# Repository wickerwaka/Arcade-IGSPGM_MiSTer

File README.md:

# This repository now lives in the [MiSTer organization](https://github.com/mister-devel/Arcade-IGSPGM_MiSTer)

# IGS PolyGame Master MiSTer FPGA core

The PolyGame Master (PGM) is an arcade system board released in 1997 by IGS. It has a lot of similarities to SNK's Neo Geo - cartridge based with multiple buses, heavily sprite focused graphics hardware, 68000 main CPU, Z80 for audio.

- Main processor: Motorola 68000 @ 20 MHz
- Sound processor: Zilog Z80 @ 8.4 MHz
- Sound chip: Wavefront ICS2115
- Graphics chip: IGS023

Games come with several flavors of protection hardware on the cartridge. Most feature an ARM7 CPU and in later games the ARM takes on a larger portion of the game update processing.

## Status
This core is currently BETA. Most games work, but the core needs more testing. The PGM platform features a large amount of variants and bootlegs that all require testing. If you encounter issues please report them via github. Save state files can be especially useful for tracking down and reproducing issues, so if you have some then please include them.

## Core Features
- Save States. The core supports save states for all games. It is expected that you can save and restore a save state at any point. If you encounter issues restoring save states, please report them.
- H-Scale. The PGM video signal tends to be squashed horizontally by consumer CRTs. In the Video Settings menu there is an H-Scale option that can be enabled which allows you to scale the width of the image up and down. This only works for analog video and does not play well with the HDMI scaler.
- NVRAM. The 128KB of main RAM on the PGM is battery backed. On the original system this is often used for bookkeeping data such as earning per game. Some games (CAVE shooters) use it for storing per-game settings. It might also be used for high score saving by some games.
- RTC. The PGM also has a battery backed clock. As far as I know this is not used by any games, but it does get displayed at startup by the BIOS. The timer can be adjusted in the BIOS, but at startup it will always be set to the MiSTers current system time.

## Supported games

- Oriental Legend
- Oriental Legend Super
- Dragon World 3
- Dragon World 3 EX
- Dragon World 2001
- The Killing Blade
- The Killing Blade Plus
- Photo Y2K
- Knights of Valour Super Heroes
- Knights of Valour 2
- Martial Masters
- Demon Front
- The Gladiator
- S.V.G. - Spectral vs Generation
- DoDonPachi II - Bee Storm
- DoDonPachi III / Dai-Ou-Jou
- Ketsui: Kizuna Jigoku Tachi
- Espgaluda

## Not yet working

- Knights of Valour
- Knights of Valour Plus
- Knights of Valour 2 Plus - Nine Dragons
- Dragon World Pretty Chance
- Happy 6-in-1

## Sources
Multiple different sources have been used as reference when developing this core.

[MAME](https://www.mamedev.org/) - Tons of information about the PGM system and especially its protection mechanisms. Also used as the source for the initial ICS2115 implementation.

[igspgm.com](https://igspgm.com/) - Motherboard images, cartridge images, archived documents. Super valuable archive of information that could easily have been lost to history.

[PGMTech](https://github.com/laoo/PGMTech) - Solid documentation of PGM memory maps and system architecture

[GUS GF1 Decap](https://github.com/nukeykt/LPC-GUS) - Coming from the same hardware lineage, the GF1 source was a useful reference for how things might be done inside the ICS2115

[Game Bub](https://github.com/elipsitz/gamebub) - ARM7TDMI implementation

## Special Thanks
Thanks to [James](https://www.retrohq.co.uk/) for all the additional insights he was able to provide. The stars aligned and we ended up exploring parts of the system as the same time. I hope I was able to help him half as much as he helped me.

Thanks to [Tim](https://igspgm.com/) for keeping valuable sources of PGM information alive on the internet over the years. It has been an invaluable source of information.

laoo, Xolod, augitesoul and everyone who has playtested, provided feedback and/or support.

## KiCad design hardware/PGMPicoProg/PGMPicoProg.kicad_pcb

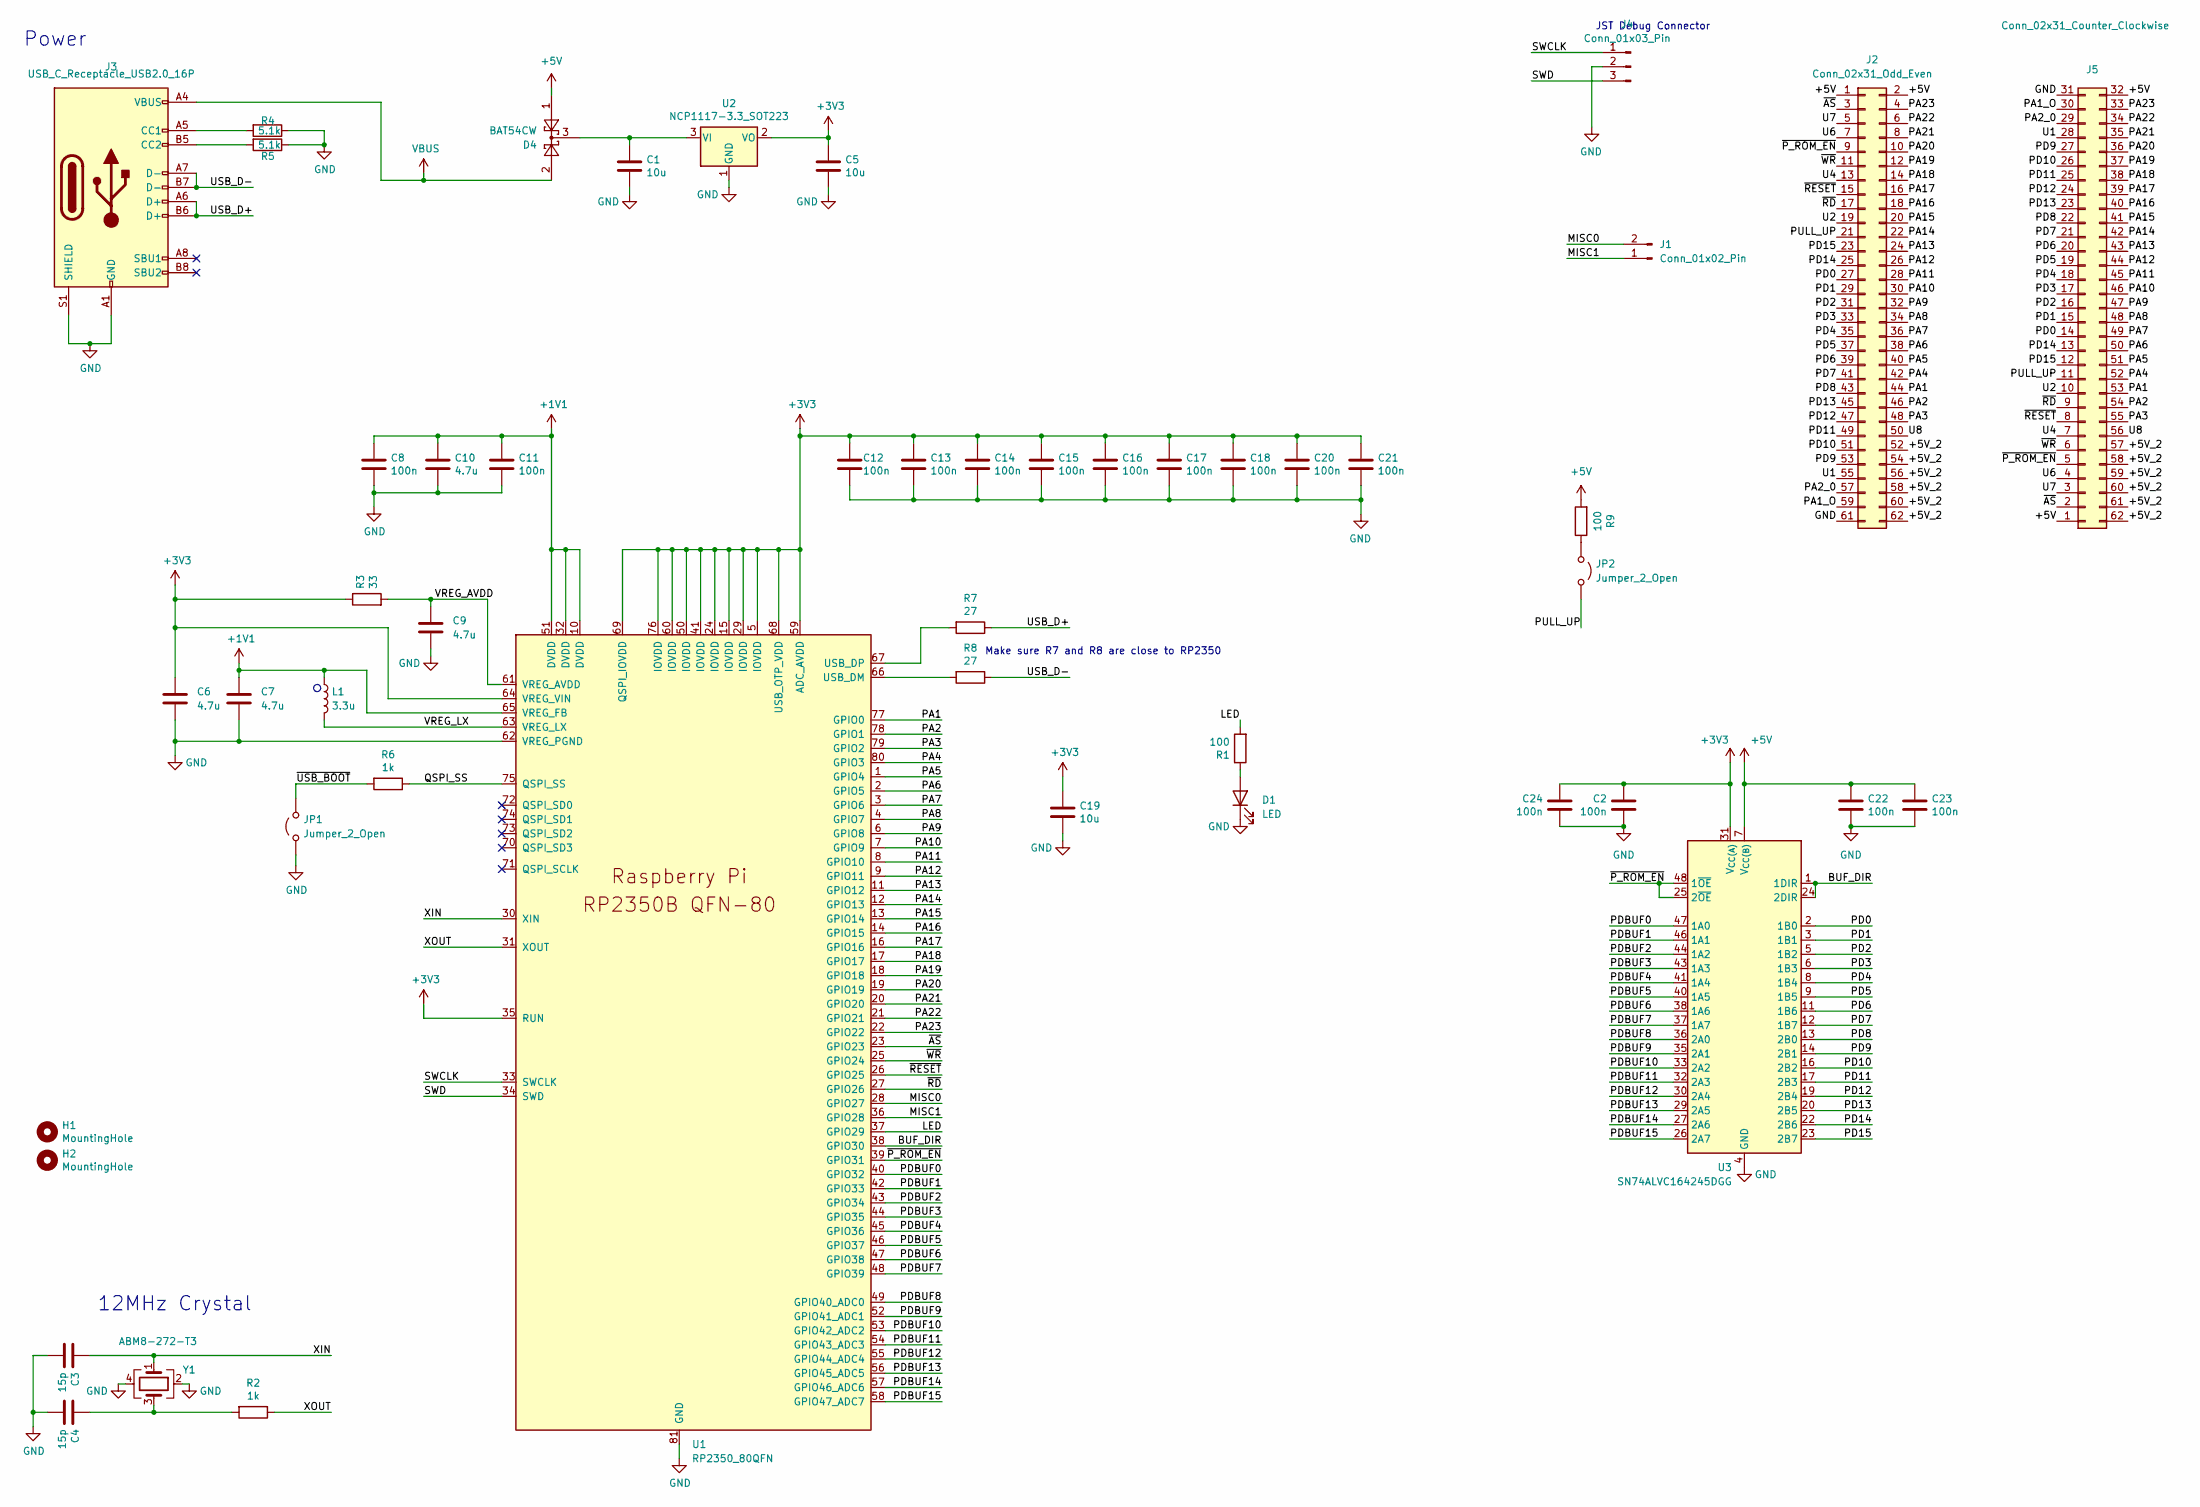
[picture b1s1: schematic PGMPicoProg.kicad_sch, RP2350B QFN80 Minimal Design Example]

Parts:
C1, C5, C19: 10u; C_0805_2012Metric; LCSC Part C15850
C2, C8, C11, C12, C13, C14, C15, C16, C17, C18, C20, C21, C22, C23, C24: 100n; C_0402_1005Metric; LCSC Part C1525
C3, C4: 15p; C_0402_1005Metric; LCSC Part C1548
C6, C7: 4.7u; C_0402_1005Metric_small_pads; LCSC Part C23733
C9, C10: 4.7u; C_0402_1005Metric; LCSC Part C23733
D1: LED; LED_0805_2012Metric; LCSC Part C2297
D4: BAT54CW; SOT-323_SC-70; MPN# C22392482; LCSC Part C22392482
H1, H2: MountingHole; MountingHole_2.7mm_M2.5
J1: Conn_01x02_Pin; PinHeader_1x02_P2.54mm_Vertical
J2: Conn_02x31_Odd_Even; PinHeader_2x31_P2.54mm_Vertical
J3: USB_C_Receptacle_USB2.0_16P; USB_C_Receptacle_G-Switch_GT-USB-7010ASV; LCSC Part C2988369
J4: Conn_01x03_Pin; PinHeader_1x03_P2.54mm_Vertical
J5: Conn_02x31_Counter_Clockwise; PGM_Cart
JP1, JP2: Jumper_2_Open; PinHeader_1x02_P2.54mm_Vertical
L1: 3.3u; L_pol_2016; LCSC Part C42411119
R1, R9: 100; R_0402_1005Metric; LCSC Part C25076
R2, R6: 1k; R_0402_1005Metric; LCSC Part C11702
R3: 33; R_0402_1005Metric; LCSC Part C25105
R4, R5: 5.1k; R_0402_1005Metric; LCSC Part C25905
R7, R8: 27; R_0402_1005Metric; LCSC Part C25100
U1: RP2350_80QFN; RP2350-QFN-80-1EP_10x10_P0.4mm_EP3.4x3.4mm_ThermalVias; LCSC Part C39843328
U2: NCP1117-3.3_SOT223; SOT-223-3_TabPin2; LCSC Part C6186
U3: SN74ALVC164245DGG; TSSOP-48_6.1x12.5mm_P0.5mm; LCSC Part C4364184
Y1: ABM8-272-T3; Crystal_SMD_3225-4Pin_3.2x2.5mm; LCSC Part C20625731

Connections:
+1V1: C7.1, C8.1, C10.1, C11.1, L1.1, U1.10 (DVDD), U1.32 (DVDD), U1.51 (DVDD), U1.65 (VREG_FB)
+3V3: C2.1, C5.1, C6.1, C12.1, C13.1, C14.1, C15.1, C16.1, C17.1, C18.1, C19.1, C20.1, C21.1, C24.1, R3.1, U1.5 (IOVDD), U1.15 (IOVDD), U1.24 (IOVDD), U1.29 (IOVDD), U1.35 (RUN), U1.41 (IOVDD), U1.50 (IOVDD), U1.59 (ADC_AVDD), U1.60 (IOVDD), U1.64 (VREG_VIN), U1.68 (USB_OTP_VDD), U1.69 (QSPI_IOVDD), U1.76 (IOVDD), U2.2 (VO), U3.31 (V_{CC(A)}), U3.42 (V_{CC(A)})
+5V: C22.1, C23.1, D4.1, J2.1, J2.2, J5.1, J5.32, R9.2, U3.7 (V_{CC(B)}), U3.18 (V_{CC(B)})
/+5V_2: J2.52, J2.54, J2.56, J2.58, J2.60, J2.62, J5.57, J5.58, J5.59, J5.60, J5.61, J5.62
/BUF_DIR: U1.38 (GPIO30), U3.1 (1DIR), U3.24 (2DIR)
/LED: R1.2, U1.37 (GPIO29)
/MISC0: J1.2, U1.28 (GPIO27)
/MISC1: J1.1, U1.36 (GPIO28)
/PA1: J2.44, J5.53, U1.77 (GPIO0)
/PA1_O: J2.59, J5.30
/PA2: J2.46, J5.54, U1.78 (GPIO1)
/PA2_0: J2.57, J5.29
/PA3: J2.48, J5.55, U1.79 (GPIO2)
/PA4: J2.42, J5.52, U1.80 (GPIO3)
/PA5: J2.40, J5.51, U1.1 (GPIO4)
/PA6: J2.38, J5.50, U1.2 (GPIO5)
/PA7: J2.36, J5.49, U1.3 (GPIO6)
/PA8: J2.34, J5.48, U1.4 (GPIO7)
/PA9: J2.32, J5.47, U1.6 (GPIO8)
/PA10: J2.30, J5.46, U1.7 (GPIO9)
/PA11: J2.28, J5.45, U1.8 (GPIO10)
/PA12: J2.26, J5.44, U1.9 (GPIO11)
/PA13: J2.24, J5.43, U1.11 (GPIO12)
/PA14: J2.22, J5.42, U1.12 (GPIO13)
/PA15: J2.20, J5.41, U1.13 (GPIO14)
/PA16: J2.18, J5.40, U1.14 (GPIO15)
/PA17: J2.16, J5.39, U1.16 (GPIO16)
/PA18: J2.14, J5.38, U1.17 (GPIO17)
/PA19: J2.12, J5.37, U1.18 (GPIO18)
/PA20: J2.10, J5.36, U1.19 (GPIO19)
/PA21: J2.8, J5.35, U1.20 (GPIO20)
/PA22: J2.6, J5.34, U1.21 (GPIO21)
/PA23: J2.4, J5.33, U1.22 (GPIO22)
/PD0: J2.27, J5.14, U3.2 (1B0)
/PD1: J2.29, J5.15, U3.3 (1B1)
/PD2: J2.31, J5.16, U3.5 (1B2)
/PD3: J2.33, J5.17, U3.6 (1B3)
/PD4: J2.35, J5.18, U3.8 (1B4)
/PD5: J2.37, J5.19, U3.9 (1B5)
/PD6: J2.39, J5.20, U3.11 (1B6)
/PD7: J2.41, J5.21, U3.12 (1B7)
/PD8: J2.43, J5.22, U3.13 (2B0)
/PD9: J2.53, J5.27, U3.14 (2B1)
/PD10: J2.51, J5.26, U3.16 (2B2)
/PD11: J2.49, J5.25, U3.17 (2B3)
/PD12: J2.47, J5.24, U3.19 (2B4)
/PD13: J2.45, J5.23, U3.20 (2B5)
/PD14: J2.25, J5.13, U3.22 (2B6)
/PD15: J2.23, J5.12, U3.23 (2B7)
/PDBUF0: U1.40 (GPIO32), U3.47 (1A0)
/PDBUF1: U1.42 (GPIO33), U3.46 (1A1)
/PDBUF2: U1.43 (GPIO34), U3.44 (1A2)
/PDBUF3: U1.44 (GPIO35), U3.43 (1A3)
/PDBUF4: U1.45 (GPIO36), U3.41 (1A4)
/PDBUF5: U1.46 (GPIO37), U3.40 (1A5)
/PDBUF6: U1.47 (GPIO38), U3.38 (1A6)
/PDBUF7: U1.48 (GPIO39), U3.37 (1A7)
/PDBUF8: U1.49 (GPIO40_ADC0), U3.36 (2A0)
/PDBUF9: U1.52 (GPIO41_ADC1), U3.35 (2A1)
/PDBUF10: U1.53 (GPIO42_ADC2), U3.33 (2A2)
/PDBUF11: U1.54 (GPIO43_ADC3), U3.32 (2A3)
/PDBUF12: U1.55 (GPIO44_ADC4), U3.30 (2A4)
/PDBUF13: U1.56 (GPIO45_ADC5), U3.29 (2A5)
/PDBUF14: U1.57 (GPIO46_ADC6), U3.27 (2A6)
/PDBUF15: U1.58 (GPIO47_ADC7), U3.26 (2A7)
/PULL_UP: J2.21, J5.11, JP2.2 (B)
/QSPI_SS: R6.1, U1.75 (QSPI_SS)
/SWCLK: J4.1, U1.33 (SWCLK)
/SWD: J4.3, U1.34 (SWD)
/U1: J2.55, J5.28
/U2: J2.19, J5.10
/U4: J2.13, J5.7
/U6: J2.7, J5.4
/U7: J2.5, J5.3
/U8: J2.50, J5.56
/USB_D+: J3.A6 (D+), J3.B6 (D+), R7.1
/USB_D-: J3.A7 (D-), J3.B7 (D-), R8.1
/VREG_AVDD: C9.1, R3.2, U1.61 (VREG_AVDD)
/VREG_LX: L1.2, U1.63 (VREG_LX)
/XIN: C3.1, U1.30 (XIN), Y1.1
/XOUT: R2.1, U1.31 (XOUT)
/~AS: J2.3, J5.2, U1.23 (GPIO23)
/~P_ROM_EN: J2.9, J5.5, U1.39 (GPIO31), U3.25 (2~OE), U3.48 (1~OE)
/~RD: J2.17, J5.9, U1.27 (GPIO26)
/~RESET: J2.15, J5.8, U1.26 (GPIO25)
/~USB_BOOT: JP1.2 (B), R6.2
/~WR: J2.11, J5.6, U1.25 (GPIO24)
GND: C1.2, C2.2, C3.2, C4.2, C5.2, C6.2, C7.2, C8.2, C9.2, C10.2, C11.2, C12.2, C13.2, C14.2, C15.2, C16.2, C17.2, C18.2, C19.2, C20.2, C21.2, C22.2, C23.2, C24.2, D1.1 (K), J2.61, J3.A1 (GND), J3.A12 (GND), J3.B1 (GND), J3.B12 (GND), J3.S1 (SHIELD), J4.2, J5.31, JP1.1 (A), R4.1, R5.1, U1.62 (VREG_PGND), U1.81 (GND), U2.1 (GND), U3.4 (GND), U3.10 (GND), U3.15 (GND), U3.21 (GND), U3.28 (GND), U3.34 (GND), U3.39 (GND), U3.45 (GND), Y1.2, Y1.4
unnamed: C4.1, R2.2, Y1.3
unnamed: D1.2 (A), R1.1
unnamed: J3.A5 (CC1), R4.2
unnamed: J3.B5 (CC2), R5.2
unnamed: JP2.1 (A), R9.1
unnamed: R8.2, U1.66 (USB_DM)
unnamed: R7.2, U1.67 (USB_DP)
unnamed: C1.1, D4.3, U2.3 (VI)
VBUS: D4.2, J3.A4 (VBUS), J3.A9 (VBUS), J3.B4 (VBUS), J3.B9 (VBUS)

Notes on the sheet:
12MHz Crystal
JST Debug Connector
Make sure R7 and R8 are close to RP2350
Power

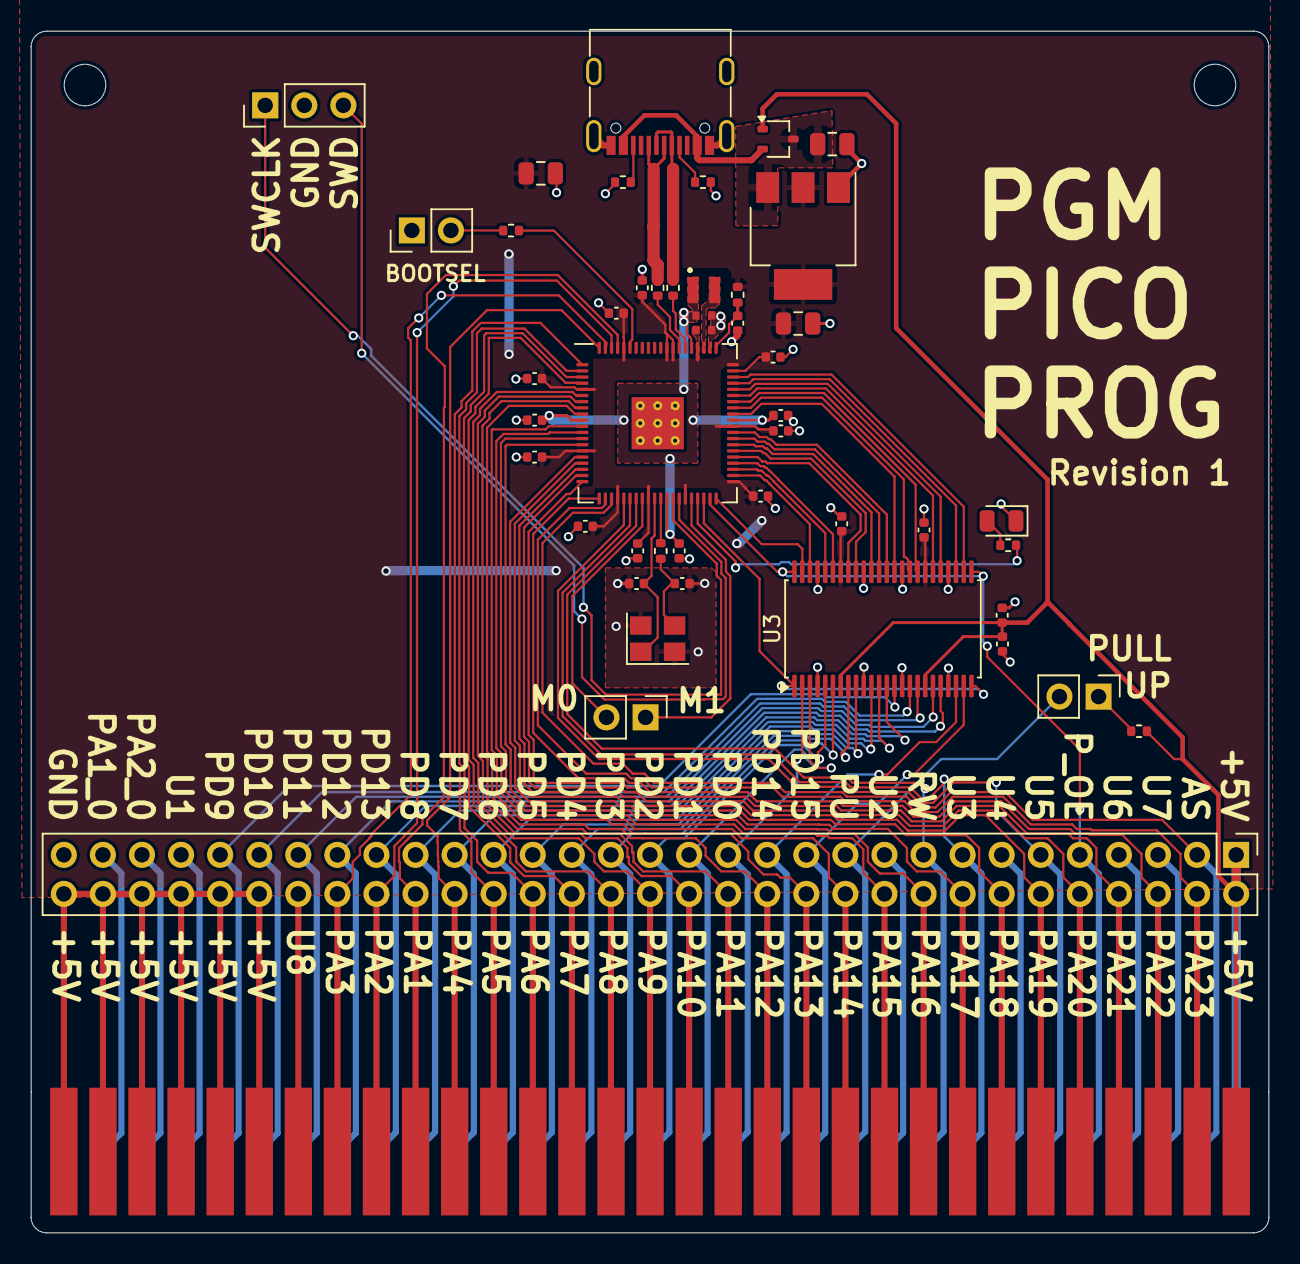
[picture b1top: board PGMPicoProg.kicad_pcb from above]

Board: 2 copper layers, 80.4 x 78.1 mm, 49 parts (0 on the bottom side), 97 nets.

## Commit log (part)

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2026-03-16 Initial commit Based on F2 core
2026-03-16 Switch IGS023 to 50Mhz clock and generate 10Mhz pixel clock internally
2026-03-21 Add some palette reading
2026-03-22 Correct h/v alignment
2026-03-22 Fixed DE-10 compilation
    Switch system clock to 50Mhz, SDRAM to 100Mhz
2026-03-22 Clean up M68000 state access in the simulator
2026-03-25 Hardware files for PGM Pico Prog and Passthrough Gartridge Module
2026-03-25 32x32 tile background layer first pass
2026-03-27 Add v3021 RTC timer and the beginnings of the Z80 related IGS026
2026-03-27 Add to files.qip
2026-03-27 Access audio RAM video igs026
2026-03-27 Rename igs026_z80 to igs026_x
2026-03-28 Sprite viewer
2026-03-29 ICS2115
2026-03-30 DE-10 fixes
2026-03-30 Fix addressing
2026-03-31 Update ICS2115 with read delay handling
2026-03-31 Flip audio endian. Fix SDR width
2026-04-11 Added additional test rom pages Fix save state support
2026-04-11 Added pgm_test rom to simulator Adjusted IRQ4 and 6 behavior to better match hardware
2026-04-12 Added test for irq4 performance. Confirmed timer continues to increment when irq is disabled. Updated core to match
2026-04-12 Scanline and IQR4 triggered on hsync
2026-04-12 refactor(sim): align naming with clang-tidy
2026-04-12 fix(pgmaudioextractor): use sdk usb reset interface
2026-04-13 Tick improvements
2026-04-13 refactor(sim): add controller API
2026-04-13 feat(sim): add stdio control protocol
2026-04-13 feat(sim): add server runtime mode
2026-04-13 feat(sim): extend agent control surface
2026-04-13 feat(sim): add VPI signal control
2026-04-13 feat(sim): add signal watches and input control
2026-04-13 refactor(sim): remove protocol exceptions
2026-04-14 fix(sim): shutdown server on eof
2026-04-14 fix(usb-audio): prevent ep panic on stream reopen
    Clear EP1 IN buffer control register in close callback to prevent
    USB_BUF_CTRL_AVAIL persisting across ISO endpoint reactivation on
    RP2040/RP2350. Also fix serial descriptor, add audio lifecycle
    instrumentation, and add reconnect-aware serial monitor tool.
2026-04-14 fix(rate): default USB sample rate to source clock
    Default the nominal capture rate to 33074 Hz and snap runtime
    measurement to the known 33074/44100 Hz source rates.
    Also update TODO.md to reflect the current MVP state and the
    remaining validation and cleanup work.
2026-04-15 refactor(capture): document and harden cdc extractor
    Document the native-rate CDC packet protocol, improve the host
    receiver with summary and gap reporting, remove the obsolete UAC
    implementation, and unify packet sequencing across audio and status
    packets.
    A 30-second strict capture check completed with zero packet and frame
    gaps on macOS.
2026-04-16 Add simulator audio capture commands and shared decoder
2026-04-16 Git ignore cleanup
2026-04-16 Naming changes for cart loading support
2026-04-17 Add cart mapping and .pgm simulator loading
2026-04-18 Enable video signals during reset
2026-04-20 Changed vram and palram to match hardware.
    Working IGS023 FG line buffer implementation. Some glitches to work out.
2026-04-21 Correct foreground behavior
2026-04-21 Audio rom cache
2026-04-24 Basic scaling test
2026-05-03 Fix V flip
2026-05-04 ICS interrupt fixes
2026-05-05 Tilemap improvements
    Give BG more time to preread rom dats
    Ensure the SDRAM req/ack is reset when switching back to FG rom reading
2026-05-07 IGS026 z80 bus arbitration changes
2026-05-09 Added ICS2115 debug UI
2026-05-09 Fix for sprites the wrap around their y-coordinate and added sprite debugging UI
2026-05-12 Tweak tilemap reads to get them more in line with hardware
2026-05-13 ASIC3 save state support
2026-05-16 Fix VRAM reads
2026-05-17 Increase line buffers and reduce queue size
2026-05-17 Sim QOL changes
    Custom rompath with env var
    Save window position and size
2026-05-19 Audio fixes
    Correct ICS2115 sample format selection
    Fix interpolation and sign extension
    Add test framework
2026-06-10 Add ketikd - Mame 0.288
2026-06-11 ketikd - add nvram
2026-06-11 Add dwpc101j working on the core
2026-06-12 Old audio tests and sim save state fix
2026-06-12 missing audio test
2026-06-12 Test rom changes for audio testing.
2026-06-12 First pass for ICS2115 validation
2026-06-12 Rollover fix
2026-06-12 missing fix
2026-06-13 Add horizontal scaler for consumer CRT width correction
    New video_hscale module re-emits each line at the full 50MHz clock (5x
    the native 10MHz pixel rate) so the active width can be scaled in 1.25%
    steps (80%..118.75%) without visible aliasing on analog output. Hsync
    is regenerated with an auto-centering shift plus a user offset control;
    parameters latch at vblank. Line buffer is a single 128x24 BRAM.
    - Hooked into video_path ahead of video_mixer; forces the scandoubler
2026-06-13 Bypass video_mixer when H-scaler is enabled
    gamma_corr inside video_mixer only advances on ce_pix rising edges (and
    serializes R/G/B through one lookup RAM, needing 4 clocks per pixel).
    With the scaler holding ce_pix at constant 1 its sync outputs latched
    once and froze, killing hsync/vsync entirely - black screen on FPGA.
    The sim never caught this because sim_top doesn't include video_path.
    Route the scaler output directly to the video_path outputs instead and
2026-06-13 Remove H-scaler from sim pipeline
    Scaler is verified working on FPGA, so it no longer needs to live in
    the Verilator build. Restore the sim-side files to their pre-scaler
    state (sim_top, build lists, sim_video, controller, protocol, docs)
    and drop the verification scripts. The scaler RTL and its FPGA-path
    integration (video_path, Arcade-IGSPGM, files.qip, mister.f) are
    unchanged.
2026-06-13 H-scale tweaks
2026-06-13 Add horizontal scaler for consumer CRT width correction
    video_hscale module to correct image width on consumer CRTs.
2026-06-13 Further audio validation work
2026-06-13 Release with ICS2115 improvements
2026-06-14 Fix mdf sync signal
2026-06-14 Fix sprite X scaling and handle 0-sized sprites
    Fixes kov2 card
    Fixes theglad sprite artifact
2026-06-14 Release 20260613
    Improved ICS2115 accuracy
    Fixed sprite scaling and 0-height sprites
    Added H-scaler
    Fixed ARM type3 savestates
2026-06-14 Fix missing first column of off screen sprites
2026-06-14 Harden voice register writes
    These were sometimes being clobbered by the readback, causing all kinds
    of random sound issues.
2026-06-14 Release with latest audio fixes
2026-06-15 MDFourier: noise stage, ping-pong sequencer, key-on volume ramp
    - Add an fmt=3 noise sweep block reusing the tone-sweep osc_fc values
    (osc_conf carried per script entry; entry widened to 8 bytes).
    - Ping-pong two voices in the Z80 timer-IRQ sequencer: pre-stage the next
    entry during the hold, key-on the staged voice at the tick, and HALT
    waiting for the IRQ -> constant latency, minimal key-on jitter.
    - Ramp volume up at key-on (vmode=2 linear, ~7.7 ms) to de-pop tone/pan/
2026-06-16 Fix timer IRQ clearing
2026-06-16 MDFourier: frame-exact sync pulses + focused sync test
    Make the sync pulses exactly one frame long so MDFourier's alignment stays
    solid: pre-stage the constant full-volume vol_acc during the non-critical
    staging step so the key-on is a single osc_ctl write (symmetric with key-off),
    and drop the ics_wait_idle settle delays from the debug driver's ICS accesses.
    Add util/mdfourier/sync_test.py: isolates just the sync pulse train, captures
    it, and measures each pulse's ON duration and following gap (sample-exact),
2026-06-16 ICS2115: voice fmt=3 is u-law, not noise
    Hardware RE on the espgalbl board shows osc_conf format 11 (both format bits
    set) decodes u-law, identical to fmt 01 -- the ULAW bit (bit0) takes priority
    over the 16BIT bit (bit1). Measured on real silicon: fmt3 and fmt1 share the
    same fundamental (390.3 vs 390.5 Hz) and RMS (~7x quieter than 8-bit/16-bit),
    and fmt3's short-loop output is periodic (it reads ROM, not a generator).
    Replace the fmt-11 LFSR noise generator in ics2115_osc.sv with u-law decode
2026-06-16 docs/ics2115: correct timer-ack and fmt=3 conclusions, audit stale notes
    Two register-matrix conclusions were wrong (both inferred from firmware usage
    and over-marked TESTED-PASS without isolating the claim on hardware):
    - 40-B timer ack: "only a full 16-bit read of the preset acks; lo8/hi8 do not
    clear" was wrong. A single low-byte read acks (BIOS HandleIrqBit0Service, the
    live z80 trace, and espgalbl all ack with one low read). The test only showed
    a 16-bit read is sufficient, never that a lone byte fails, and contradicted
2026-06-16 ICS2115: host osc IRQ pend requires bit7 AND bit5 (matrix 00-C)
    Hardware (matrix 00-C): a host osc_conf write latches an osc IRQ pend only when
    both bit7 (PEND) and bit5 (IRQ enable) are set (0xA0); 0x80 alone is a no-op.
    The RTL pended on bit7 alone, so an osc_conf write carrying a stale bit7 could
    spuriously latch a pend. Gate the host-write pend on bit7 AND bit5. Update the
    00-C matrix entry (was mis-marked TESTED-PASS despite the noted divergence).
2026-06-16 docs/ics2115: hardware retest of 00-C / P0-C / 10-D / P2-A
    Re-ran the four entries flagged in the matrix audit on real hardware
    (util/irq_matrix_retest.py, single-voice probes via ics_remote):
    - 10-D CONFIRMED: osc_ctl readback = 0xFC | (written & 0x03) (upper-6 forced 1,
    bits 1:0 stored); matches RTL.
    - P2-A CONFIRMED: a lone low-byte write only latches; a lone high-byte write
    commits {hi, latched_lo}; matches the RTL low-latch/high-commit scheme.
2026-06-17 docs/ics2115: resolve 00-C — bit5 (enable), not bit7 (pend), gates the osc IRQ
    Pursued 00-C on hardware with an IRQ-counter probe (util/host_pend_probe.py) on
    a stopped voice; the Z80 osc-IRQ counter is the reliable detector (IRQV/0x4B are
    drained by the Z80 handler). Reproducible: osc_conf 0x80 (bit7 only) -> 0 IRQs;
    0xA0 (bit7+bit5) -> fires; 0x20 (bit5 only, no bit7) -> also fires (fixed at 2
    over 50-500ms, not a storm).
    So the discriminator is bit5 (IRQ-enable), NOT bit7 (the "pend" status bit): bit7
2026-06-17 MDFourier: 4s pre-roll silence before the sequence starts
    Hold ~4 s of silence after MDF_START before entry 0 plays, so the external audio
    capture is fully running before the (sync-pulse) start.
    - z80_ics_driver.c: MDF_START_DELAY_FRAMES (240 ticks ~= 4.0s at the ~59.9 Hz
    timer); mdf_start arms the timer and sets mdf_delay instead of starting entry
    0; mdf_tick counts the pre-roll down and calls mdf_begin_entry0() when it hits
    0. Applies to both the host-driven (ics_remote) and standalone pages.
2026-06-17 CPU ROM in DDR
2026-06-17 Missing files
2026-06-17 Fix IRQV pending status
2026-06-17 Add more variants
2026-06-17 MDFourier: continuous fc-only tone sweep, finer steps, drop pan sweep
    Simplify the tone sweep and fix the playback dropout: one voice now plays
    continuously and only osc_fc changes per step, instead of keying each tone
    on/off. Keying voices on/off every tick during playback raced the chip's voice
    sequencer and occasionally lost a write, silencing a voice at a deterministic
    point in the sweep (a host-write vs voice-RAM collision; a settle delay only
    shifted it). Retuning a looping voice via osc_fc is one write per step with no
2026-06-17 Tweak ICS2115 clock to more closely match measured hardware clock
2026-06-18 Update readme and organize MRAs
